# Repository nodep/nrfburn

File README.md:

# nrfburn
This is a hardware and software package for flashing Nordic Semiconductors nRF24LE1 and nRF24LU1+ microcontrollers. It consists of three parts: the flasher device with a USB connection, the firmware running on the flasher, and a host program which sends command to the flasher over the USB connection.

### The flasher

The flasher is based around an Atmel AVR ATmega88pa microcontroller running at 12MHz and 3.3V. The PCB is a mixture of through-hole and SMD components chosen as a compromise between size, ease of hand-soldering and mechanical robustness.

It has connectors with pin configurations which allow two popular nRF24LU1+ breakouts and dongles to be directly plugged into the flasher. One is the SparkFun Tranciever Breakout - nRF24LU1+, and the other is the popular nRF USB dongle from ebay.

It also has an 8 pin flat cable connector through which it can flash nRF24LE1 devices as an in-system programmer.

The DBG_LU1 output can be used as a UART debug output from the nRF24LU1+ dongle. There are also two LEDs (DBG1 and DBG2) which can be driven from the SparkFun breakout. This is also useful for debugging.

### The firmware

The flasher firmware communicates with the host PC though [obdev's V-USB](https://www.obdev.at/products/vusb/index.html). It accepts commands from the PC, executes them and sends responses.

### The host PC

The program running on the host PC is a cross-platform (Windows and Linux) command line tool. It does not need special OS drivers because all communication is done through the USB HID class. It's been tested on Windows 7, 8 and 10 and on Linux running on Hardkernel's Odroid X2 board.

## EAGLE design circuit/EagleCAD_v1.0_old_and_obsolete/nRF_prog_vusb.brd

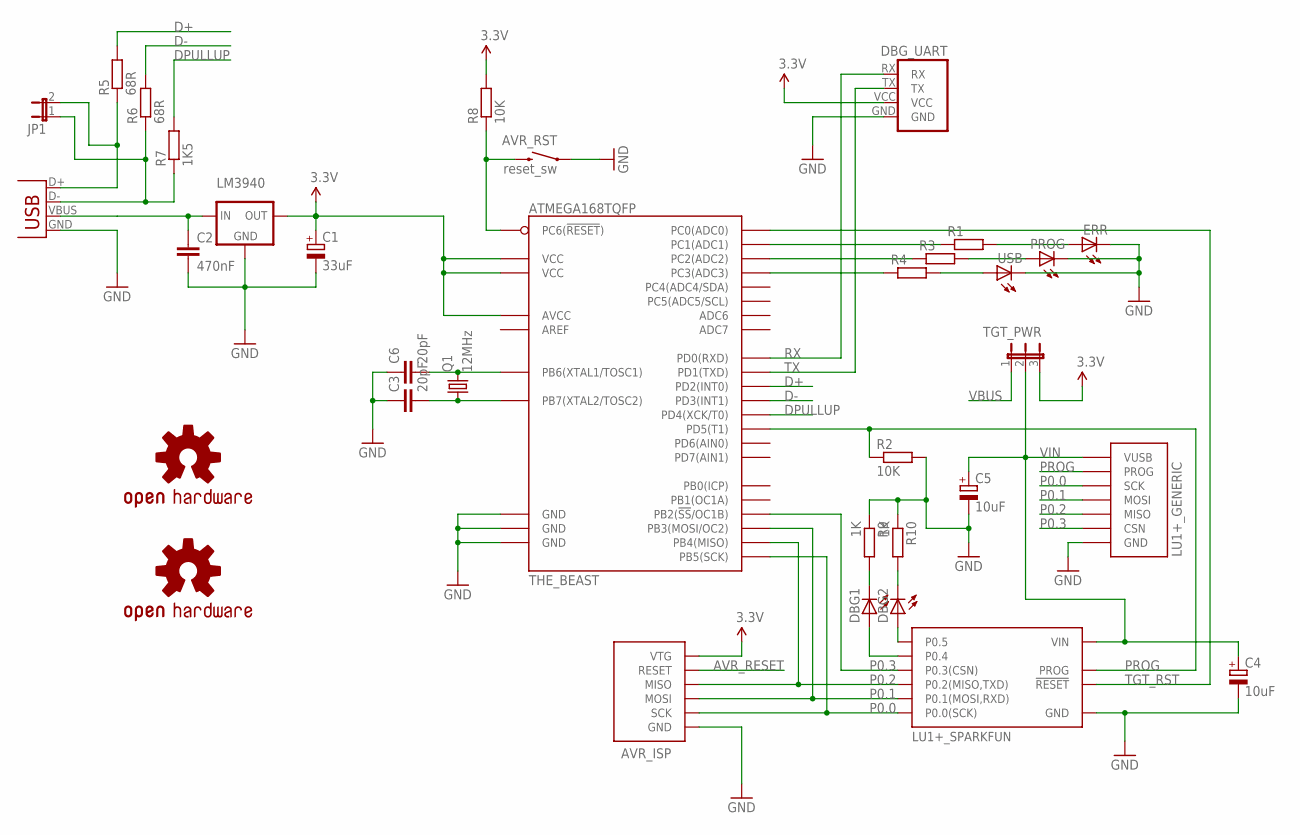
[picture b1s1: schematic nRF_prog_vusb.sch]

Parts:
AVR_ISP: AVR-ISP-6SMALL_FP; AVR-ISP-6-SMALL-FP
AVR_RST: reset_sw; TACTILE_SWITCH_SMD
C1: 33uF; SMC_B
C2: 470nF; C0805K
C3, C6: 20pF; C0805
C4, C5: 10uF; SMC_B
DBG1, DBG2: LEDCHIPLED_0805; CHIPLED_0805
DBG_UART: UART_PORT
ERR: LEDCHIPLED_0805; CHIPLED_0805
JP1: JP1E; JP1
LM3940: LM3940; SOT223
LU1+_GENERIC: NRF24LU1P_GENERIC
LU1+_SPARKFUN: NRF24LU1P_SPARKFUN_BREAKOUT; NRF24LU+_SPARKFUN_BREAKOUT
PROG: LEDCHIPLED_0805; CHIPLED_0805
Q1: 12MHz; QUARTZ
R1, R3, R4: R-EU_M0805; M0805
R2, R8: 10K; M0805
R5, R6: 68R; M0805
R7: 1K5; M0805
R9, R10: 1K; M0805
TGT_PWR: JP2E; JP2
THE_BEAST: ATMEGA168TQFP; TQFP32-08
U$1: OSHW-LOGOM; OSHW-LOGO-M
U$2: OSHW-LOGOL; OSHW-LOGO-L
USB: LEDCHIPLED_0805; CHIPLED_0805
USB-B: USBPTH; USB-B-PTH

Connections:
3.3V: AVR_ISP.VCC (VTG), C1.+, DBG_UART.VCC, LM3940.3 (OUT), R8.2, TGT_PWR.3, THE_BEAST.4 (VCC), THE_BEAST.6 (VCC), THE_BEAST.18 (AVCC)
AVR_RESET: AVR_ISP.RESET, AVR_RST.3 (2), R8.1, THE_BEAST.29 (PC6(!RESET!))
D+: R5.2, THE_BEAST.32 (PD2(INT0))
D-: R6.2, THE_BEAST.1 (PD3(INT1))
DPULLUP: R7.2, THE_BEAST.2 (PD4(XCK/T0))
GND: AVR_ISP.GND, AVR_RST.1, C1.-, C2.2, C3.1, C4.-, C5.-, C6.1, DBG_UART.GND, ERR.C, LM3940.2 (GND), LM3940.4 (GND), LU1+_GENERIC.GND, LU1+_SPARKFUN.GND, PROG.C, R2.2, R9.1, R10.1, THE_BEAST.3 (GND), THE_BEAST.5 (GND), THE_BEAST.21 (GND), USB.C, USB-B.GND
unnamed: DBG2.A, LU1+_SPARKFUN.P0.5
unnamed: DBG1.A, LU1+_SPARKFUN.P0.4
unnamed: DBG2.C, R10.2
unnamed: DBG1.C, R9.2
unnamed: R4.1, THE_BEAST.26 (PC3(ADC3))
unnamed: R3.1, THE_BEAST.25 (PC2(ADC2))
unnamed: R1.1, THE_BEAST.24 (PC1(ADC1))
unnamed: R4.2, USB.A
unnamed: PROG.A, R3.2
unnamed: ERR.A, R1.2
unnamed: C6.2, Q1.2, THE_BEAST.7 (PB6(XTAL1/TOSC1))
unnamed: C3.2, Q1.1, THE_BEAST.8 (PB7(XTAL2/TOSC2))
P0.0: AVR_ISP.SCK, LU1+_GENERIC.SCK, LU1+_SPARKFUN.P0.0 (P0.0(SCK)), THE_BEAST.17 (PB5(SCK))
P0.1: AVR_ISP.MOSI, LU1+_GENERIC.MOSI, LU1+_SPARKFUN.P0.1 (P0.1(MOSI,RXD)), THE_BEAST.15 (PB3(MOSI/OC2))
P0.2: AVR_ISP.MISO, LU1+_GENERIC.MISO, LU1+_SPARKFUN.P0.2 (P0.2(MISO,TXD)), THE_BEAST.16 (PB4(MISO))
P0.3: LU1+_GENERIC.CSN, LU1+_SPARKFUN.P0.3 (P0.3(CSN)), THE_BEAST.14 (PB2(!SS!/OC1B))
PROG: LU1+_GENERIC.PROG, LU1+_SPARKFUN.PROG, R2.1, THE_BEAST.9 (PD5(T1))
RX: DBG_UART.RX, THE_BEAST.30 (PD0(RXD))
TGT_RST: LU1+_SPARKFUN.RESET (!RESET!), THE_BEAST.23 (PC0(ADC0))
TX: DBG_UART.TX, THE_BEAST.31 (PD1(TXD))
USB_D+: JP1.2, R5.1, USB-B.D+
USB_D-: JP1.1, R6.1, R7.1, USB-B.D-
VBUS: C2.1, LM3940.1 (IN), TGT_PWR.1, USB-B.VBUS
VIN: C4.+, C5.+, LU1+_GENERIC.VUSB, LU1+_SPARKFUN.VIN, TGT_PWR.2

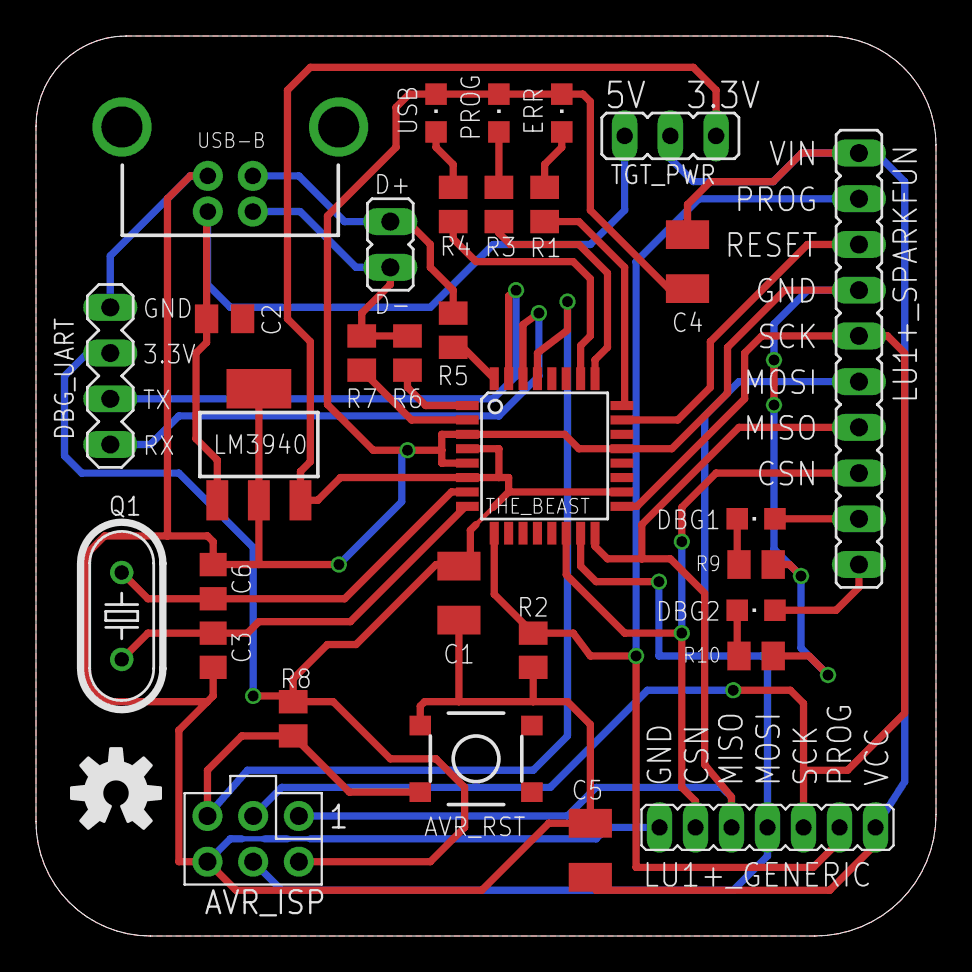
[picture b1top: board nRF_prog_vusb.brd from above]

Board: 2 copper layers, 50.0 x 50.0 mm, 34 parts (1 on the bottom side), 30 nets.

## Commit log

2015-11-03 initial circuit commit
2015-11-03 firmware and software
2016-02-26 Added flasher images
2016-02-26 Testing images
2016-02-26 Add some text to README.md
2016-02-26 File and folder name cleanup
2016-02-26 KiCad schematic and PCB for usable with the new KiCad release (4.0.1)
2016-08-07 added missing files
2016-08-09 debug logging added
2016-11-07 added licence
2020-06-29 replaced auto_ptr<> with vector<>
2025-02-16 moved HW design to KiCad 8
2025-02-16 added 3D models

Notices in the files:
parts and their libraries:
SparkFun: Licensing: CC v3.0 Share-Alike You are welcome to use this library for commercial purposes.
